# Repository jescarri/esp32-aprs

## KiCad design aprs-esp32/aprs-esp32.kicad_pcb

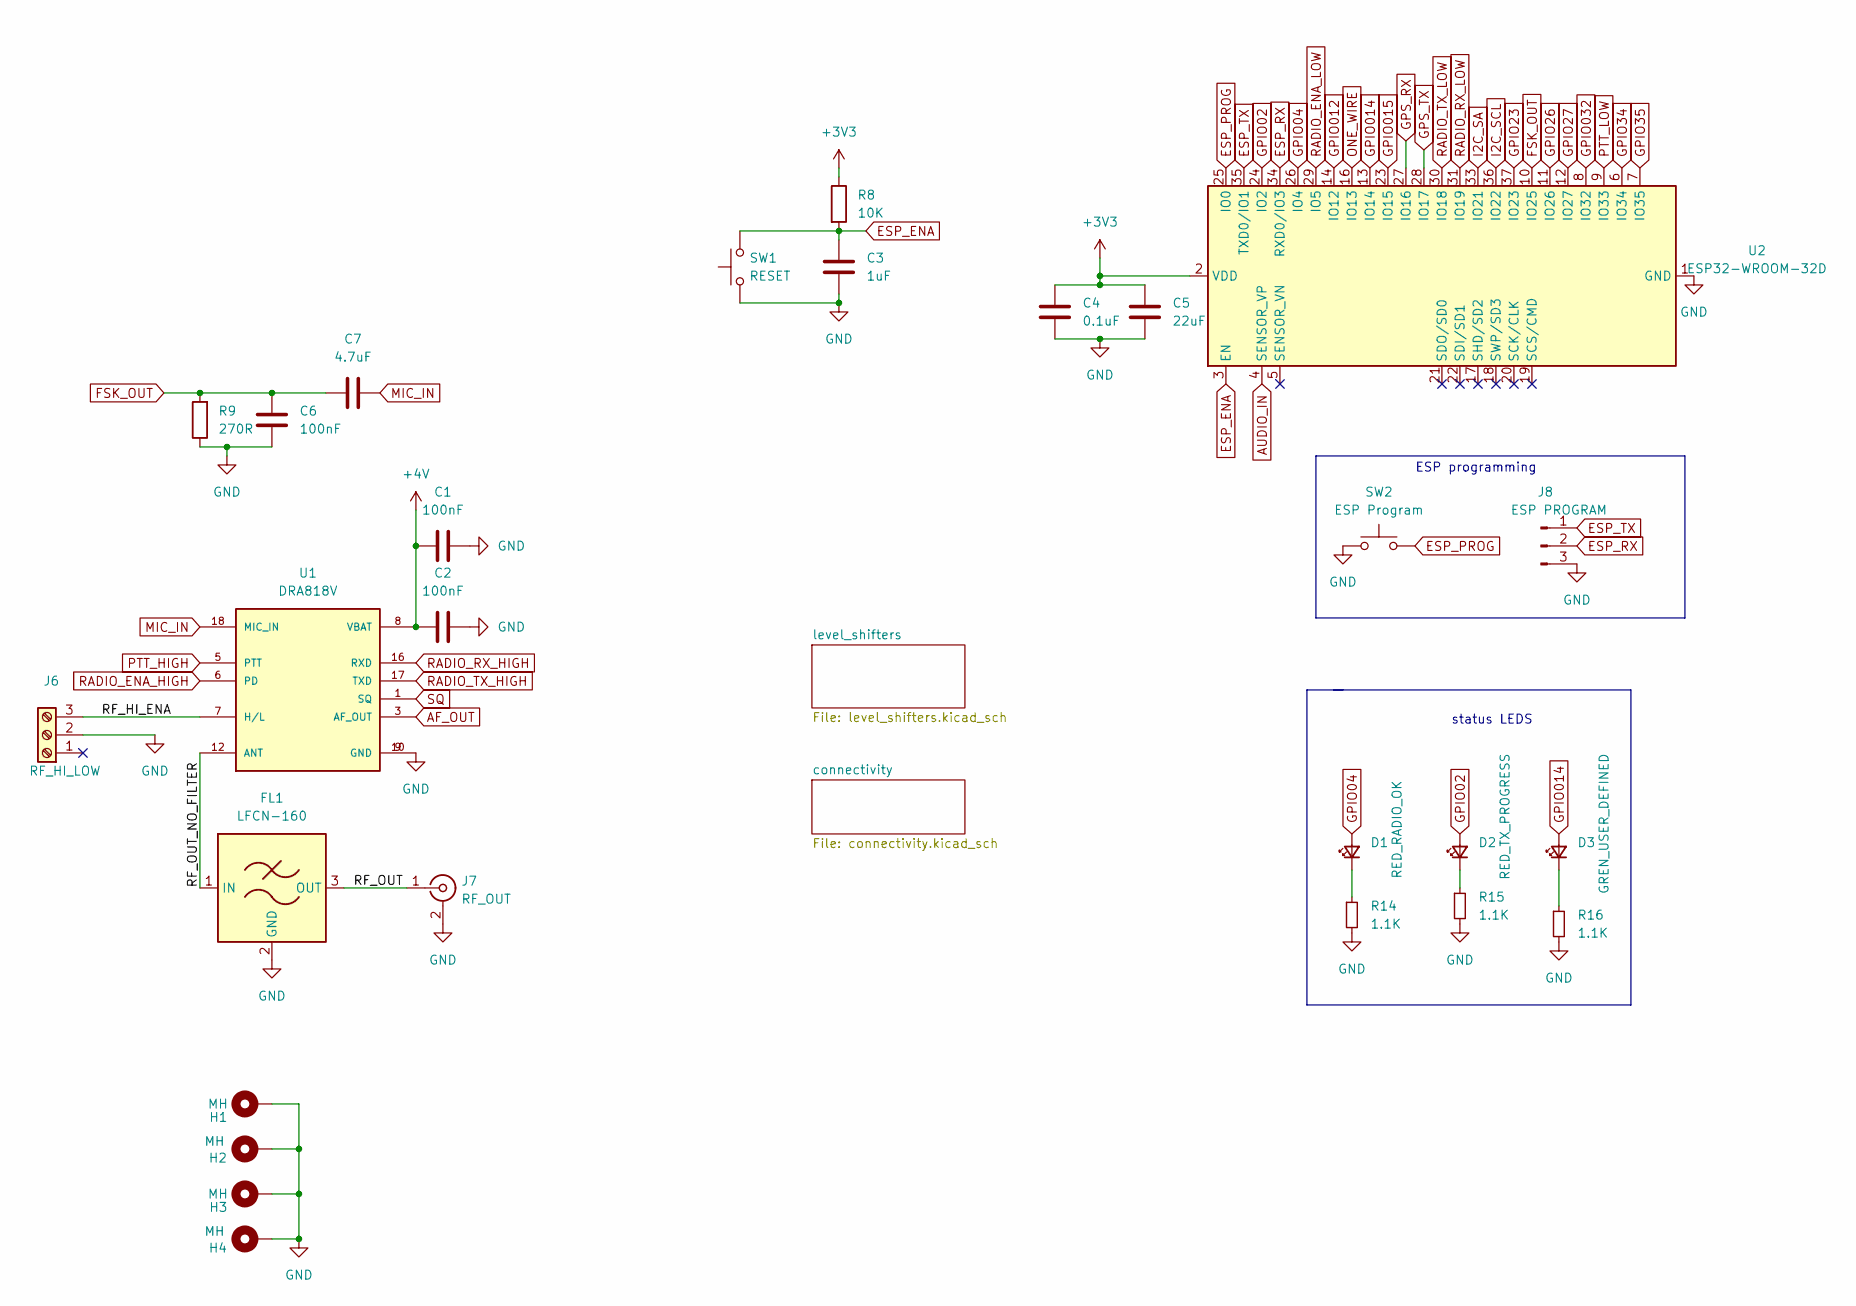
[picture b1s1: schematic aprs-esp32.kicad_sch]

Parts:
C1, C2, C6: 100nF; C_1206_3216Metric_Pad1.33x1.80mm_HandSolder
C3: 1uF; C_1812_4532Metric_Pad1.57x3.40mm_HandSolder
C4: 0.1uF; C_1812_4532Metric_Pad1.57x3.40mm_HandSolder
C5: 22uF; CP_EIA-3528-21_Kemet-B_Pad1.50x2.35mm_HandSolder
C7: 4.7uF; C_1206_3216Metric_Pad1.33x1.80mm_HandSolder
D1: RED_RADIO_OK; LED_0603_1608Metric_Pad1.05x0.95mm_HandSolder
D2: RED_TX_PROGRESS; LED_0603_1608Metric_Pad1.05x0.95mm_HandSolder
D3: GREN_USER_DEFINED; LED_0603_1608Metric_Pad1.05x0.95mm_HandSolder
FL1: LFCN-160; Filter_Mini-Circuits_FV1206
H1, H2, H3, H4: MH; MountingHole_4.3mm_M4_Pad_Via
J6: RF_HI_LOW; PinHeader_1x03_P2.54mm_Vertical
J7: RF_OUT; SMA_Amphenol_132291_Vertical
J8: ESP PROGRAM; PinHeader_1x03_P2.54mm_Vertical
R8: 10K; R_1206_3216Metric_Pad1.30x1.75mm_HandSolder
R9: 270R; R_1206_3216Metric_Pad1.30x1.75mm_HandSolder
R14, R15, R16: 1.1K; R_1206_3216Metric_Pad1.30x1.75mm_HandSolder
SW1: RESET; SW_PUSH_6mm_H5mm
SW2: ESP Program; SW_PUSH_6mm_H5mm
U1: DRA818V; DORJI_DRA818V; PART_REV 1.23
U2: ESP32-WROOM-32D; ESP32-WROOM-32

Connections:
+3V3: C4.1, C5.1, R8.1, U2.2 (VDD); also elsewhere on the board
+4V: C1.1, C2.1, U1.8 (VBAT); also elsewhere on the board
/RF_HI_ENA: J6.3, U1.7 (H/L)
/RF_OUT: FL1.3 (OUT), J7.1 (In)
/RF_OUT_NO_FILTER: FL1.1 (IN), U1.12 (ANT)
AF_OUT: U1.3 (AF_OUT); also elsewhere on the board
AUDIO_IN: U2.4 (SENSOR_VP); also elsewhere on the board
ESP_ENA: C3.1, R8.2, SW1.2, U2.3 (EN)
ESP_PROG: SW2.2, U2.25 (IO0)
ESP_RX: J8.2, U2.34 (RXD0/IO3)
ESP_TX: J8.1, U2.35 (TXD0/IO1)
FSK_OUT: C6.2, C7.2, R9.2, U2.10 (IO25)
GND: C1.2, C2.2, C3.2, C4.2, C5.2, C6.1, FL1.2 (GND), FL1.4 (GND), H1.1, H2.1, H3.1, H4.1, J6.2, J7.2 (Ext), J8.3, R9.1, R14.2, R15.2, R16.2, SW1.1, SW2.1, U1.9 (GND), U1.10 (GND), U2.1 (GND), U2.15 (GND), U2.38 (GND), U2.39 (GND); also elsewhere on the board
GPIO02: D2.2 (A), U2.24 (IO2)
GPIO04: D1.2 (A), U2.26 (IO4)
GPIO012: U2.14 (IO12); also elsewhere on the board
GPIO014: D3.2 (A), U2.13 (IO14)
GPIO015: U2.23 (IO15); also elsewhere on the board
GPIO23: U2.37 (IO23); also elsewhere on the board
GPIO26: U2.11 (IO26); also elsewhere on the board
GPIO27: U2.12 (IO27); also elsewhere on the board
GPIO032: U2.8 (IO32); also elsewhere on the board
GPIO34: U2.6 (IO34); also elsewhere on the board
GPIO35: U2.7 (IO35); also elsewhere on the board
GPS_RX: U2.27 (IO16); also elsewhere on the board
GPS_TX: U2.28 (IO17); also elsewhere on the board
I2C_SA: U2.33 (IO21); also elsewhere on the board
I2C_SCL: U2.36 (IO22); also elsewhere on the board
MIC_IN: C7.1, U1.18 (MIC_IN)
unnamed: D1.1 (K), R14.1
unnamed: D2.1 (K), R15.1
unnamed: D3.1 (K), R16.1
ONE_WIRE: U2.16 (IO13); also elsewhere on the board
PTT_HIGH: U1.5 (PTT); also elsewhere on the board
PTT_LOW: U2.9 (IO33); also elsewhere on the board
RADIO_ENA_HIGH: U1.6 (PD); also elsewhere on the board
RADIO_ENA_LOW: U2.29 (IO5); also elsewhere on the board
RADIO_RX_HIGH: U1.16 (RXD); also elsewhere on the board
RADIO_RX_LOW: U2.31 (IO19); also elsewhere on the board
RADIO_TX_HIGH: U1.17 (TXD); also elsewhere on the board
RADIO_TX_LOW: U2.30 (IO18); also elsewhere on the board
SQ: U1.1 (SQ); also elsewhere on the board

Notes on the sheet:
ESP programming
status LEDS

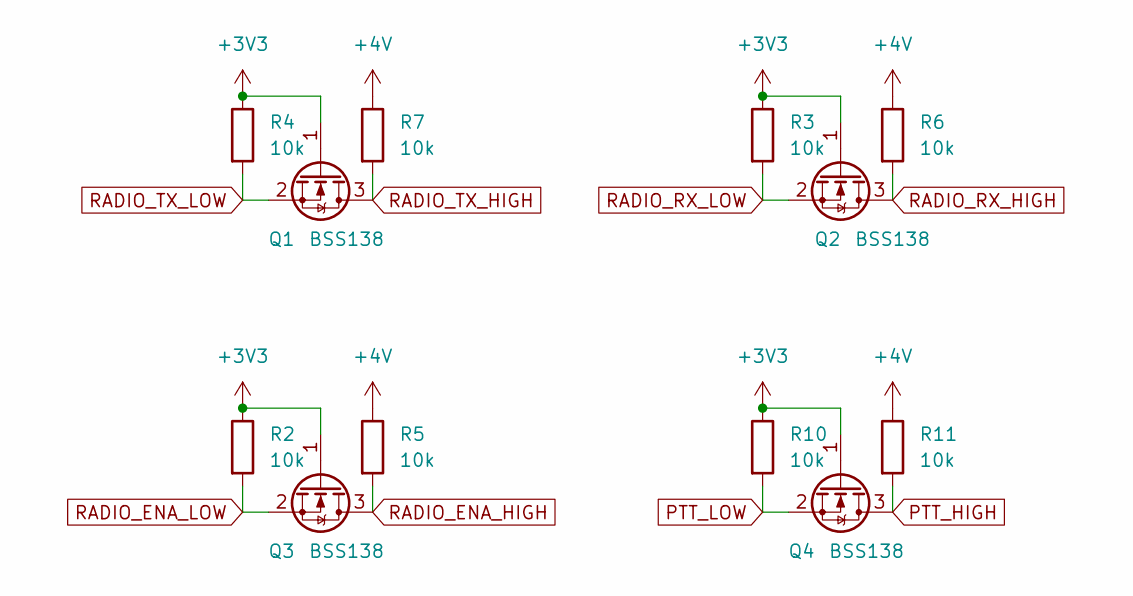
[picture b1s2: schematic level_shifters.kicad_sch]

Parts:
Q1, Q2, Q3, Q4: BSS138; SOT-23
R2, R3, R4, R5, R6, R7, R10, R11: 10k; R_1206_3216Metric_Pad1.30x1.75mm_HandSolder

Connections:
+3V3: Q1.1 (G), Q2.1 (G), Q3.1 (G), Q4.1 (G), R2.1, R3.1, R4.1, R10.1; also elsewhere on the board
+4V: R5.1, R6.1, R7.1, R11.1; also elsewhere on the board
PTT_HIGH: Q4.3 (D), R11.2; also elsewhere on the board
PTT_LOW: Q4.2 (S), R10.2; also elsewhere on the board
RADIO_ENA_HIGH: Q3.3 (D), R5.2; also elsewhere on the board
RADIO_ENA_LOW: Q3.2 (S), R2.2; also elsewhere on the board
RADIO_RX_HIGH: Q2.3 (D), R6.2; also elsewhere on the board
RADIO_RX_LOW: Q2.2 (S), R3.2; also elsewhere on the board
RADIO_TX_HIGH: Q1.3 (D), R7.2; also elsewhere on the board
RADIO_TX_LOW: Q1.2 (S), R4.2; also elsewhere on the board

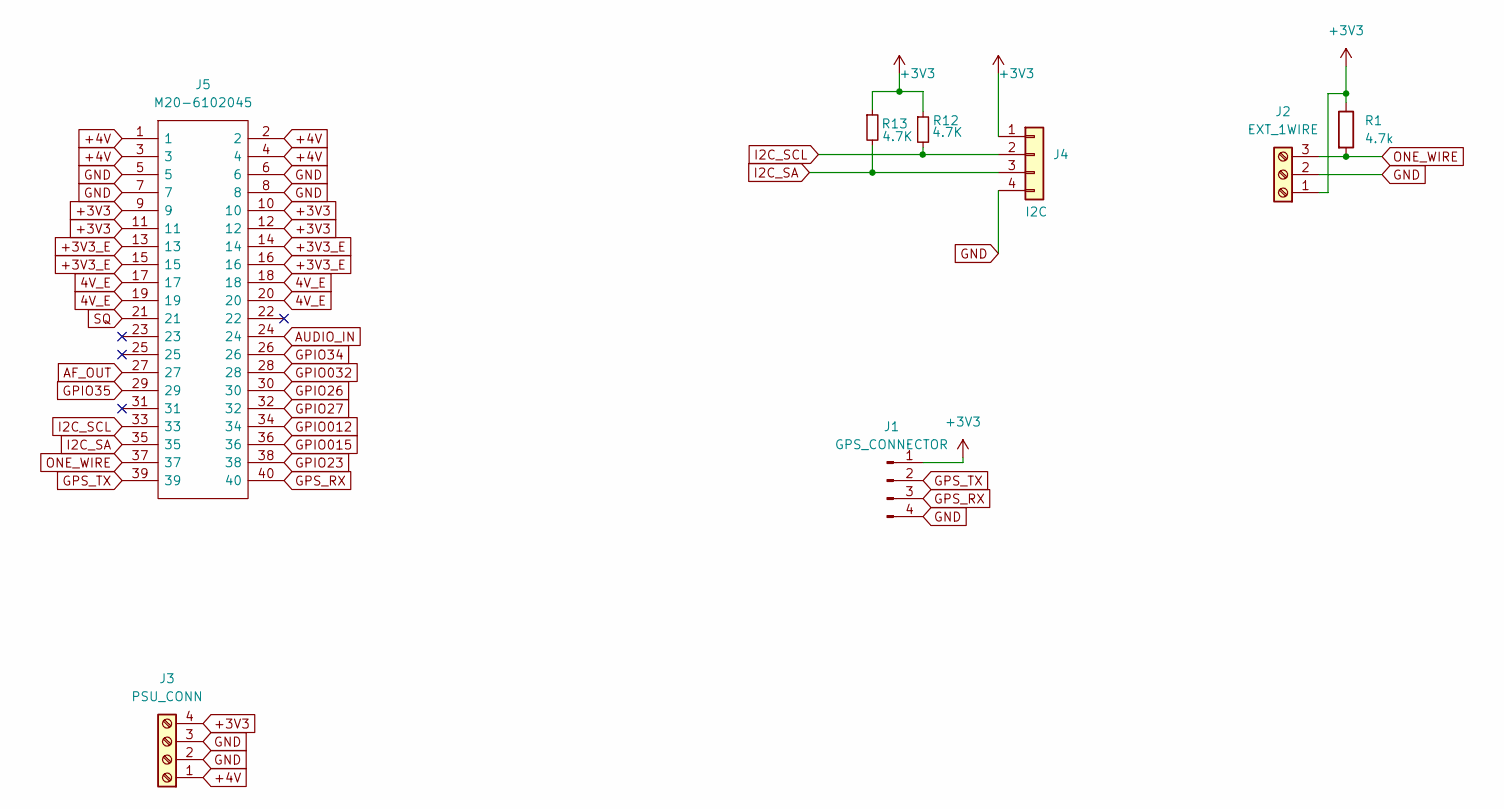
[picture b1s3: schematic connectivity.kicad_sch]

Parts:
J1: GPS_CONNECTOR; PinHeader_1x04_P2.54mm_Vertical
J2: EXT_1WIRE; PinHeader_1x03_P2.54mm_Vertical
J3: PSU_CONN; TerminalBlock_Altech_AK300-4_P5.00mm
J4: I2C; PinHeader_1x04_P2.54mm_Vertical
J5: M20-6102045; RHDR40W66P254_2X20_5146X500X1105P; Manufacturer_Part_Number M20-6102045; Mouser Part Number 855-M20-6102045
R1: 4.7k; R_1206_3216Metric_Pad1.30x1.75mm_HandSolder
R12, R13: 4.7K; R_1206_3216Metric_Pad1.30x1.75mm_HandSolder

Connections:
4V_E: J5.17, J5.18, J5.19, J5.20
+3V3: J1.1, J2.1, J3.4, J4.1, J5.9, J5.10, J5.11, J5.12, R1.1, R12.1, R13.1; also elsewhere on the board
+3V3_E: J5.13, J5.14, J5.15, J5.16
+4V: J3.1, J5.1, J5.2, J5.3, J5.4; also elsewhere on the board
AF_OUT: J5.27; also elsewhere on the board
AUDIO_IN: J5.24; also elsewhere on the board
GND: J1.4, J2.2, J3.2, J3.3, J4.4, J5.5, J5.6, J5.7, J5.8; also elsewhere on the board
GPIO012: J5.34; also elsewhere on the board
GPIO015: J5.36; also elsewhere on the board
GPIO23: J5.38; also elsewhere on the board
GPIO26: J5.30; also elsewhere on the board
GPIO27: J5.32; also elsewhere on the board
GPIO032: J5.28; also elsewhere on the board
GPIO34: J5.26; also elsewhere on the board
GPIO35: J5.29; also elsewhere on the board
GPS_RX: J1.3, J5.40; also elsewhere on the board
GPS_TX: J1.2, J5.39; also elsewhere on the board
I2C_SA: J4.3, J5.35, R13.2; also elsewhere on the board
I2C_SCL: J4.2, J5.33, R12.2; also elsewhere on the board
ONE_WIRE: J2.3, J5.37, R1.2; also elsewhere on the board
SQ: J5.21; also elsewhere on the board

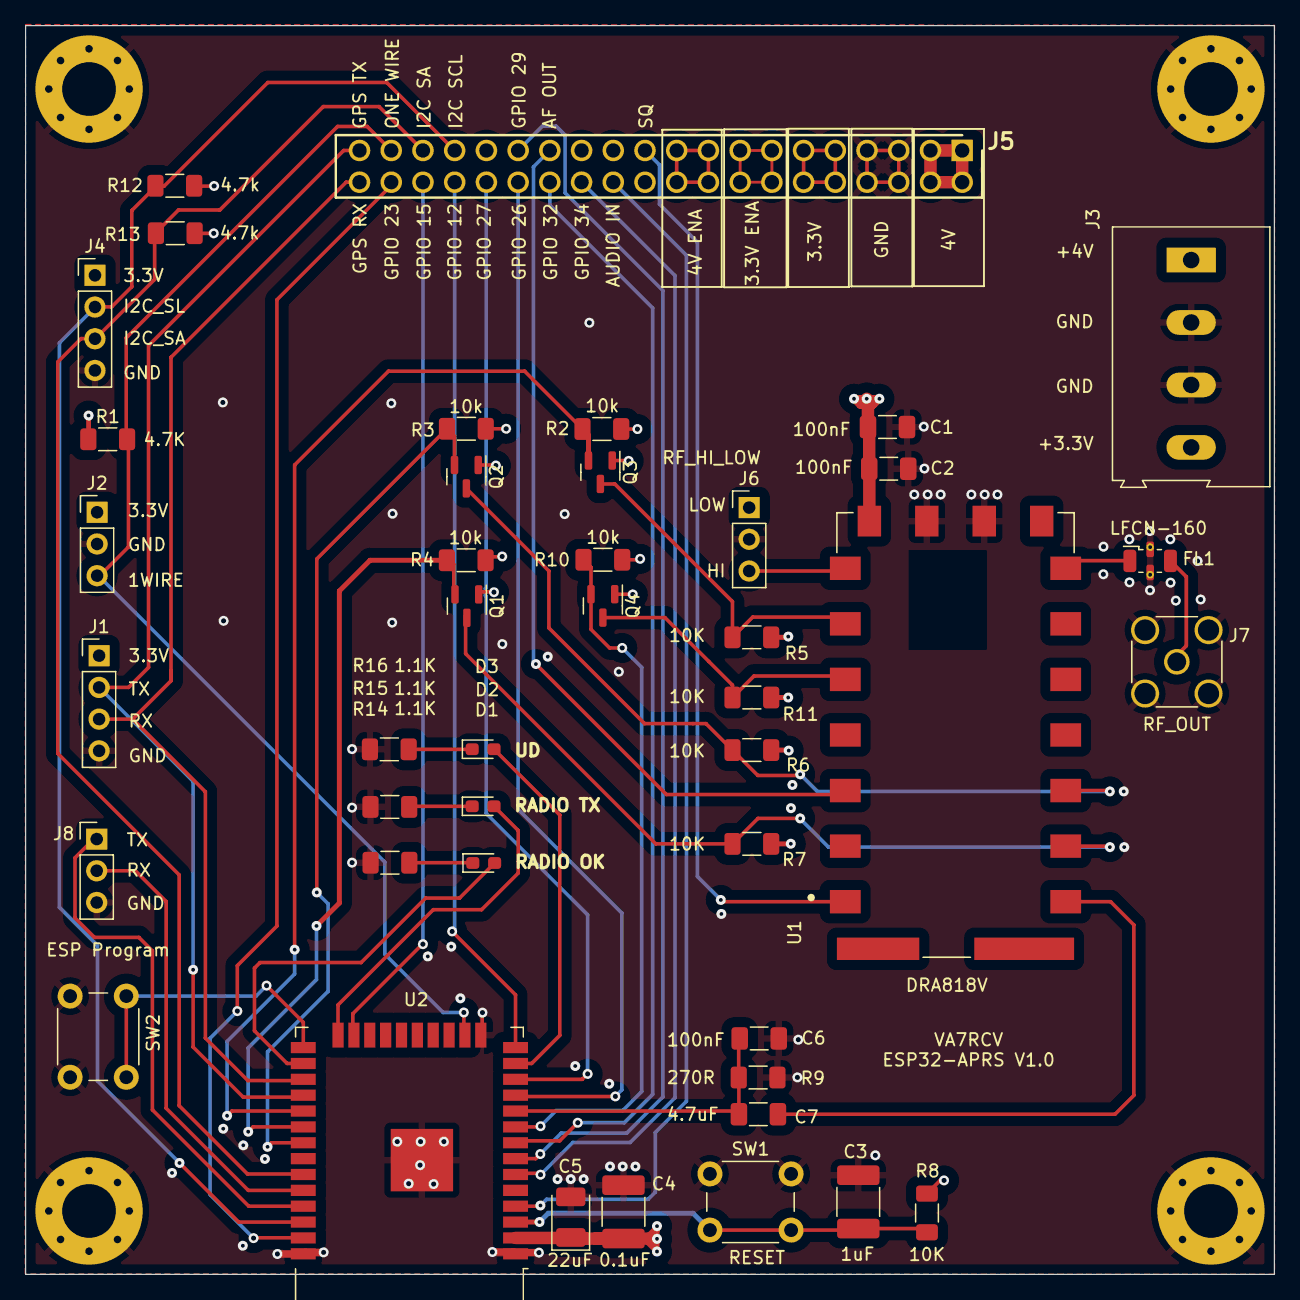
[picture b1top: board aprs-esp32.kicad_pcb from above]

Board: 4 copper layers, 100.0 x 100.0 mm, 47 parts (0 on the bottom side), 44 nets.

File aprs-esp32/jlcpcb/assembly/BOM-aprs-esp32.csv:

Comment,Designator,Footprint,LCSC
100nF,"C1,C2",C_1206_3216Metric_Pad1.33x1.80mm_HandSolder,C24497
I2C,J4,PinHeader_1x04_P2.54mm_Vertical,
DRA818V,U1,DORJI_DRA818V,
ESP Program,SW2,SW_PUSH_6mm_H5mm,
RESET,SW1,SW_PUSH_6mm_H5mm,
4.7K,R13,R_1206_3216Metric_Pad1.30x1.75mm_HandSolder,
4.7K,R12,R_1206_3216Metric_Pad1.30x1.75mm_HandSolder,
10k,R11,R_1206_3216Metric_Pad1.30x1.75mm_HandSolder,
10k,R10,R_1206_3216Metric_Pad1.30x1.75mm_HandSolder,
270R,R9,R_1206_3216Metric_Pad1.30x1.75mm_HandSolder,
10K,R8,R_1206_3216Metric_Pad1.30x1.75mm_HandSolder,
10k,R7,R_1206_3216Metric_Pad1.30x1.75mm_HandSolder,
10k,R6,R_1206_3216Metric_Pad1.30x1.75mm_HandSolder,
10k,R5,R_1206_3216Metric_Pad1.30x1.75mm_HandSolder,
10k,R4,R_1206_3216Metric_Pad1.30x1.75mm_HandSolder,
10k,R3,R_1206_3216Metric_Pad1.30x1.75mm_HandSolder,
10k,R2,R_1206_3216Metric_Pad1.30x1.75mm_HandSolder,
4.7k,R1,R_1206_3216Metric_Pad1.30x1.75mm_HandSolder,
BSS138,Q4,SOT-23,
BSS138,Q3,SOT-23,
BSS138,Q2,SOT-23,
BSS138,Q1,SOT-23,
M20-6102045,J5,RHDR40W66P254_2X20_5146X500X1105P,
PSU_CONN,J3,TerminalBlock_Altech_AK300-4_P5.00mm,
EXT_1WIRE,J2,PinHeader_1x03_P2.54mm_Vertical,
GPS_CONNECTOR,J1,PinHeader_1x04_P2.54mm_Vertical,
LFCN-160,FL1,Filter_Mini-Circuits_FV1206,
4.7uF,C7,C_1206_3216Metric_Pad1.33x1.80mm_HandSolder,
100nF,C6,C_1206_3216Metric_Pad1.33x1.80mm_HandSolder,
22uF,C5,CP_EIA-3528-21_Kemet-B_Pad1.50x2.35mm_HandSolder,
0.1uF,C4,C_1812_4532Metric_Pad1.57x3.40mm_HandSolder,
1uF,C3,C_1812_4532Metric_Pad1.57x3.40mm_HandSolder,
RED_RADIO_OK,D1,LED_0603_1608Metric_Pad1.05x0.95mm_HandSolder,
RF_OUT,J7,SMA_Amphenol_132291_Vertical,
1.1K,R14,R_1206_3216Metric_Pad1.30x1.75mm_HandSolder,
RED_TX_PROGRESS,D2,LED_0603_1608Metric_Pad1.05x0.95mm_HandSolder,
GREN_USER_DEFINED,D3,LED_0603_1608Metric_Pad1.05x0.95mm_HandSolder,
1.1K,R15,R_1206_3216Metric_Pad1.30x1.75mm_HandSolder,
ESP PROGRAM,J8,PinHeader_1x03_P2.54mm_Vertical,
RF_HI_LOW,J6,PinHeader_1x03_P2.54mm_Vertical,
MH,H4,MountingHole_4.3mm_M4_Pad_Via,
MH,H3,MountingHole_4.3mm_M4_Pad_Via,
1.1K,R16,R_1206_3216Metric_Pad1.30x1.75mm_HandSolder,
MH,H2,MountingHole_4.3mm_M4_Pad_Via,
MH,H1,MountingHole_4.3mm_M4_Pad_Via,
ESP32-WROOM-32D,U2,ESP32-WROOM-32,

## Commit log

2022-06-19 limpieza de esquematico
    movi los level shifters a su propia pagina
    movi la mayor parte de los conectores a una pagina separada
    corregido: simbolos de pin desconectado faltantes
    cambio: ESP renombrado a u2
2022-06-19 multiple cambios en el ruteo
    Todas las reglas de DRC pasan. solo hay warnings debido al silk screen
    correcciones PCB:
    - VDD para ESP y DRA ruteado via capacitores
    - multiple conecciones a VDD cambiadas para evitar tombstoning
    Optimizaciones PCB:
    - algunos tracks fueron ruteados para reducir largo.
2022-06-20 pcb actualizado
    - leds de status estan ahora juntos y visibles
    - level shifters estan ahora juntos al centro
    - capacitores de bypass estan ruteados correctamente.
    - capacitores de bypass estan ordenados correctamente (valor ascendnte desde el circuito)
    - lineas i2c estan ruteadas mas lejos del borde del pcb.
2022-07-01 cambios a la lineas de poder
    -Modifique la isla de 4v para que sea mas peque;a
    -Cambie el ruteo de varios tracks para hacerlos mas cortos
    -modificado la ubicacion de algunas vias para que las lineas de tierra esten mas cercanas a los pads
    -capacitores de bypass de ESP estan 1mm mas cerca.
2022-07-20 ADDED: ground vias en donde la sen~al cambia de plano
